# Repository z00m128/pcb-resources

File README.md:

# My PCB library 
Here is the set of printed circuit boards created by me over a time. I used mostly KiCad (PCBs created from scratch) or Sprint-Layout 6.0 (PCBs recreated from scans or photos).

## [ZX Spectrum 128k replica](https://github.com/z00m128/pcb-resources/tree/main/Toastrack)
Recreated PCB of ZX Spectrum 128k. I felt sorry for the Toastrack owner who contacted me with a repair request and who fell victim to eBay fraud, so I decided to make a replica.

## [ZX Cherry Keyboard](https://github.com/z00m128/pcb-resources/blob/main/ZX-Cherry-KB/)
Another iteration of a mechanical keyboard for the ZX Spectrum. This time my own, designed for one of my projects, but it is compatible with +2/+3 case.

## [Didaktik M'92](https://github.com/z00m128/pcb-resources/tree/main/Didaktik-M-92)
A clone of the ZX Spectrum computer manufactured by the Slovak company Didaktik v.d. in the early 1990s. The recreated PCB has been verified and is functional.

## [Didaktik Kompakt, revision 2.3](https://github.com/z00m128/pcb-resources/tree/main/Didaktik-Kompakt-ver23)
A clone of the ZX Spectrum computer manufactured by the Slovak company Didaktik v.d. in the early 1990s. This clone is actually a Didaktik M with a built-in D80 disk system running the MDOS operating system. The recreated PCB has been verified and is functional.

## Melodik 2, revisions [1.0](https://github.com/z00m128/pcb-resources/tree/main/Melodik2/v1.0), [1.1](https://github.com/z00m128/pcb-resources/tree/main/Melodik2/v1.1) and [2.0](https://github.com/z00m128/pcb-resources/tree/main/Melodik2/v2.0)
Melodik was an audio interface for the ZX Spectrum and compatibles, manufactured by Didaktik v.d. during the 1990s. It was of poor quality, suffered from several ailments and broke down. These were my 3 attempts to recreate it so that the result fit into the original box. The revisions differ only minimally and are a consequence of KiCad not being able to properly open projects created in its older versions. All have a fixed oscillator error, removed collision with D40 / D80 / Kompakt floppy controllers. The latest revision 2.0 is not tested but should be functional. It has an added filter in the LM386 power supply.

## KeyFace
A PS/2 keyboard interface for ZX Spectrum, [internal](https://github.com/z00m128/pcb-resources/tree/main/KeyFace) and [external](https://github.com/z00m128/pcb-resources/tree/main/KeyFace-external) versions. Both were developed by MDV in late 90's for Kompakt Servis company. Both PCBs are verified and working.

## [Lamac CPM](https://github.com/z00m128/pcb-resources/tree/main/Lamac-CPM)
A board used to modify a ZX Spectrum computer to expand memory (80k-256k) for use with CP/M. It was common modification in former Czechoslovakia, well documented in local electronics magazine. This PCB was not vertified yet.

## [PMD ColorAce](https://github.com/z00m128/pcb-resources/tree/main/PMD-ColorAce)
Hardware modification for PMD85 computer. It extends its capabilities and allows to display 7 different colors on the black background. This is my own iteration of PCB. It was not verified yet.

## [PMD KeyFace](https://github.com/z00m128/pcb-resources/tree/main/PMD-KeyFace)
PS/2 keyboard interface for PMD85 computer. This is my own iteration of PCB. It was not verified yet.

## [Kicad libraries](https://github.com/z00m128/pcb-resources/tree/main/KiCad-libs)
Set of libraries for KiCad 6.0 and newer that you may need if you want to edit some of my projects.

_GAL20V8, GAL22V10, AY-3-8912, AY-3-8910, ZX Spectrum expansion connector._

---

## NOTICE
The production of these printed circuit boards for profit is strictly prohibited. See [license](LICENSE.md).

## Disclaimer
_All PCBs posted here are just my hobby projects and not professional designs. They may contain errors, glitches, or other unforeseen problems. Some of them have been tested quite extensively, but I make no warranties as to functionality or fitness for a particular purpose. If you connect any of these products to any of your equipment, you do so entirely at your own risk and I am not responsible for any damages._

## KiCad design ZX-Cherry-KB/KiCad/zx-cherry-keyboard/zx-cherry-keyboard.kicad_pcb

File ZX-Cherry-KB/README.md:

# ZX Cherry Keyboard

I needed a proper mechanical keyboard for one of my projects and none of the freely available solutions suited me. So I decided to design my own keyboard, but in a way that it would be usable elsewhere, not just in my project. This keyboard is compatible with the ZX Spectrum +2 (gray) and should work also with other ZX Spectrums and clones. With ZX Spectrum +2A/+3 it is not tested, but the base matrix is connected identical to other Spectrums, so it should work too.

Due to the hard-to-find 4.5u spacebar, the key layout has been changed to the easier-to-find 6.25u spacebar. I also swapped the BREAK and DELETE keys and moved EDIT and other keys to make it more comfortable for me.

With [these](https://www.thingiverse.com/thing:4978541) keycaps it fits nicely to +2 case, see the prototype photos below.

## Top Layer

## Bottom Layer

## Custom Layout

## Prototype pictures

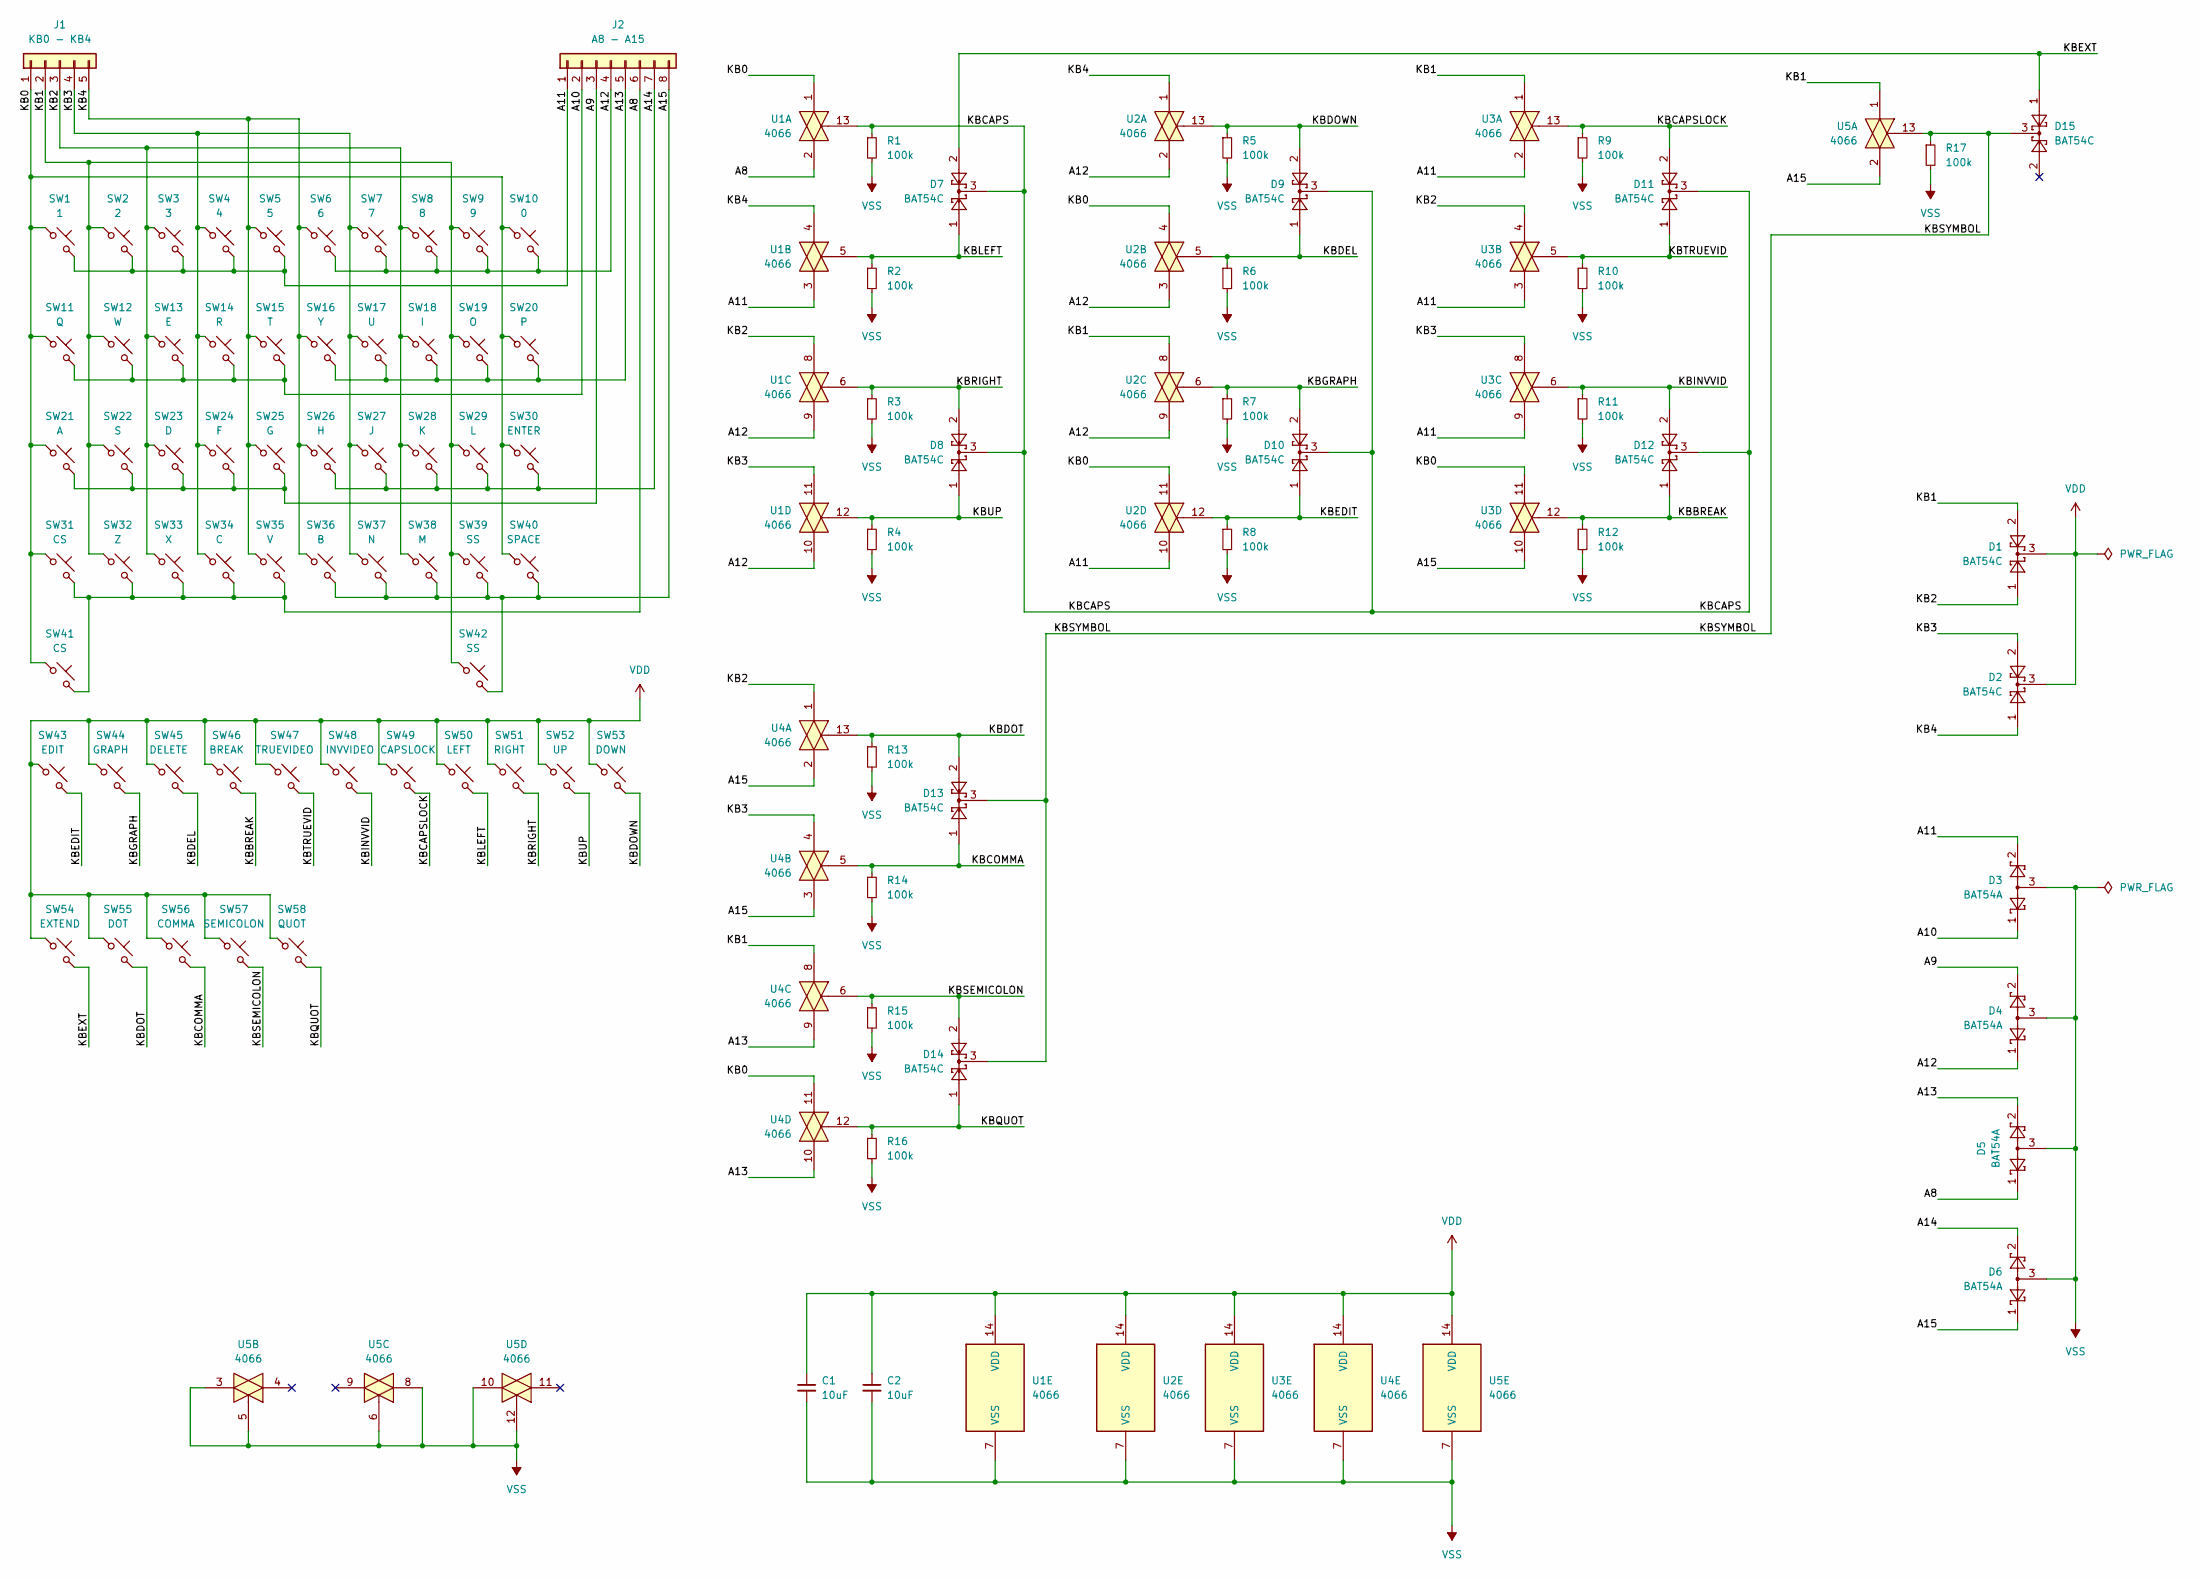
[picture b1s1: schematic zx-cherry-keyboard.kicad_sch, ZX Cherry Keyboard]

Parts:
C1, C2: 10uF; C_1210_3225Metric_Pad1.33x2.70mm_HandSolder
D1, D2, D7, D8, D9, D10, D11, D12, D13, D14, D15: BAT54C; SOT-23
D3, D4, D5, D6: BAT54A; SOT-23
J1: KB0 - KB4; PinHeader_1x05_P2.54mm_Horizontal
J2: A8 - A15; PinHeader_1x08_P2.54mm_Horizontal
R1, R2, R3, R4, R5, R6, R7, R8, R9, R10, R11, R12, R13, R14, R15, R16, R17: 100k; R_1206_3216Metric_Pad1.30x1.75mm_HandSolder
SW1: 1; SW_Cherry_MX_1.00u_PCB
SW2: 2; SW_Cherry_MX_1.00u_PCB
SW3: 3; SW_Cherry_MX_1.00u_PCB
SW4: 4; SW_Cherry_MX_1.00u_PCB
SW5: 5; SW_Cherry_MX_1.00u_PCB
SW6: 6; SW_Cherry_MX_1.00u_PCB
SW7: 7; SW_Cherry_MX_1.00u_PCB
SW8: 8; SW_Cherry_MX_1.00u_PCB
SW9: 9; SW_Cherry_MX_1.00u_PCB
SW10: 0; SW_Cherry_MX_1.00u_PCB
SW11: Q; SW_Cherry_MX_1.00u_PCB
SW12: W; SW_Cherry_MX_1.00u_PCB
SW13: E; SW_Cherry_MX_1.00u_PCB
SW14: R; SW_Cherry_MX_1.00u_PCB
SW15: T; SW_Cherry_MX_1.00u_PCB
SW16: Y; SW_Cherry_MX_1.00u_PCB
SW17: U; SW_Cherry_MX_1.00u_PCB
SW18: I; SW_Cherry_MX_1.00u_PCB
SW19: O; SW_Cherry_MX_1.00u_PCB
SW20: P; SW_Cherry_MX_1.00u_PCB
SW21: A; SW_Cherry_MX_1.00u_PCB
SW22: S; SW_Cherry_MX_1.00u_PCB
SW23: D; SW_Cherry_MX_1.00u_PCB
SW24: F; SW_Cherry_MX_1.00u_PCB
SW25: G; SW_Cherry_MX_1.00u_PCB
SW26: H; SW_Cherry_MX_1.00u_PCB
SW27: J; SW_Cherry_MX_1.00u_PCB
SW28: K; SW_Cherry_MX_1.00u_PCB
SW29: L; SW_Cherry_MX_1.00u_PCB
SW30: ENTER; SW_Cherry_MX_1.75u_PCB
SW31: CS; SW_Cherry_MX_1.75u_PCB
SW32: Z; SW_Cherry_MX_1.00u_PCB
SW33: X; SW_Cherry_MX_1.00u_PCB
SW34: C; SW_Cherry_MX_1.00u_PCB
SW35: V; SW_Cherry_MX_1.00u_PCB
SW36: B; SW_Cherry_MX_1.00u_PCB
SW37: N; SW_Cherry_MX_1.00u_PCB
SW38: M; SW_Cherry_MX_1.00u_PCB
SW39, SW42: SS; SW_Cherry_MX_1.00u_PCB
SW40: SPACE; SW_Cherry_MX_6.25u_PCB
SW41: CS; SW_Cherry_MX_1.50u_PCB
SW43: EDIT; SW_Cherry_MX_1.00u_PCB
SW44: GRAPH; SW_Cherry_MX_1.00u_PCB
SW45: DELETE; SW_Cherry_MX_1.25u_PCB
SW46: BREAK; SW_Cherry_MX_1.25u_PCB
SW47: TRUEVIDEO; SW_Cherry_MX_1.00u_PCB
SW48: INVVIDEO; SW_Cherry_MX_1.00u_PCB
SW49: CAPSLOCK; SW_Cherry_MX_1.00u_PCB
SW50: LEFT; SW_Cherry_MX_1.00u_PCB
SW51: RIGHT; SW_Cherry_MX_1.00u_PCB
SW52: UP; SW_Cherry_MX_1.00u_PCB
SW53: DOWN; SW_Cherry_MX_1.00u_PCB
SW54: EXTEND; SW_Cherry_MX_1.50u_PCB
SW55: DOT; SW_Cherry_MX_1.00u_PCB
SW56: COMMA; SW_Cherry_MX_1.00u_PCB
SW57: SEMICOLON; SW_Cherry_MX_1.00u_PCB
SW58: QUOT; SW_Cherry_MX_1.00u_PCB
U1, U2, U3, U4, U5: 4066; SO-14_5.3x10.2mm_P1.27mm

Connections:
/A8: D5.1, J2.6, SW31.2, SW32.2, SW33.2, SW34.2, SW35.2, SW41.2, U1.2
/A9: D4.2, J2.3, SW21.2, SW22.2, SW23.2, SW24.2, SW25.2
/A10: D3.1, J2.2, SW11.2, SW12.2, SW13.2, SW14.2, SW15.2
/A11: D3.2, J2.1, SW1.2, SW2.2, SW3.2, SW4.2, SW5.2, U1.3, U2.10, U3.2, U3.3, U3.9
/A12: D4.1, J2.4, SW6.2, SW7.2, SW8.2, SW9.2, SW10.2, U1.9, U1.10, U2.2, U2.3, U2.9
/A13: D5.2, J2.5, SW16.2, SW17.2, SW18.2, SW19.2, SW20.2, U4.9, U4.10
/A14: D6.2, J2.7, SW26.2, SW27.2, SW28.2, SW29.2, SW30.2
/A15: D6.1, J2.8, SW36.2, SW37.2, SW38.2, SW39.2, SW40.2, SW42.2, U3.10, U4.2, U4.3, U5.2
/KB0: J1.1, SW1.1, SW10.1, SW11.1, SW20.1, SW21.1, SW30.1, SW31.1, SW40.1, SW41.1, U1.1, U2.4, U2.11, U3.11, U4.11
/KB1: D1.2, J1.2, SW2.1, SW9.1, SW12.1, SW19.1, SW22.1, SW29.1, SW32.1, SW39.1, SW42.1, U2.8, U3.1, U4.8, U5.1
/KB2: D1.1, J1.3, SW3.1, SW8.1, SW13.1, SW18.1, SW23.1, SW28.1, SW33.1, SW38.1, U1.8, U3.4, U4.1
/KB3: D2.2, J1.4, SW4.1, SW7.1, SW14.1, SW17.1, SW24.1, SW27.1, SW34.1, SW37.1, U1.11, U3.8, U4.4
/KB4: D2.1, J1.5, SW5.1, SW6.1, SW15.1, SW16.1, SW25.1, SW26.1, SW35.1, SW36.1, U1.4, U2.1
/KBBREAK: D12.1, R12.1, SW46.2, U3.12
/KBCAPS: D7.3, D8.3, D9.3, D10.3, D11.3, D12.3, R1.1, U1.13
/KBCAPSLOCK: D11.2, R9.1, SW49.2, U3.13
/KBCOMMA: D13.1, R14.1, SW56.2, U4.5
/KBDEL: D9.1, R6.1, SW45.2, U2.5
/KBDOT: D13.2, R13.1, SW55.2, U4.13
/KBDOWN: D9.2, R5.1, SW53.2, U2.13
/KBEDIT: D10.1, R8.1, SW43.2, U2.12
/KBEXT: D7.2, D15.1, SW54.2
/KBGRAPH: D10.2, R7.1, SW44.2, U2.6
/KBINVVID: D12.2, R11.1, SW48.2, U3.6
/KBLEFT: D7.1, R2.1, SW50.2, U1.5
/KBQUOT: D14.1, R16.1, SW58.2, U4.12
/KBRIGHT: D8.2, R3.1, SW51.2, U1.6
/KBSEMICOLON: D14.2, R15.1, SW57.2, U4.6
/KBSYMBOL: D13.3, D14.3, D15.3, R17.1, U5.13
/KBTRUEVID: D11.1, R10.1, SW47.2, U3.5
/KBUP: D8.1, R4.1, SW52.2, U1.12
VDD: C1.1, C2.1, D1.3, D2.3, SW43.1, SW44.1, SW45.1, SW46.1, SW47.1, SW48.1, SW49.1, SW50.1, SW51.1, SW52.1, SW53.1, SW54.1, SW55.1, SW56.1, SW57.1, SW58.1, U1.14 (VDD), U2.14 (VDD), U3.14 (VDD), U4.14 (VDD), U5.14 (VDD)
VSS: C1.2, C2.2, D3.3, D4.3, D5.3, D6.3, R1.2, R2.2, R3.2, R4.2, R5.2, R6.2, R7.2, R8.2, R9.2, R10.2, R11.2, R12.2, R13.2, R14.2, R15.2, R16.2, R17.2, U1.7 (VSS), U2.7 (VSS), U3.7 (VSS), U4.7 (VSS), U5.3, U5.5, U5.6, U5.7 (VSS), U5.8, U5.10, U5.12

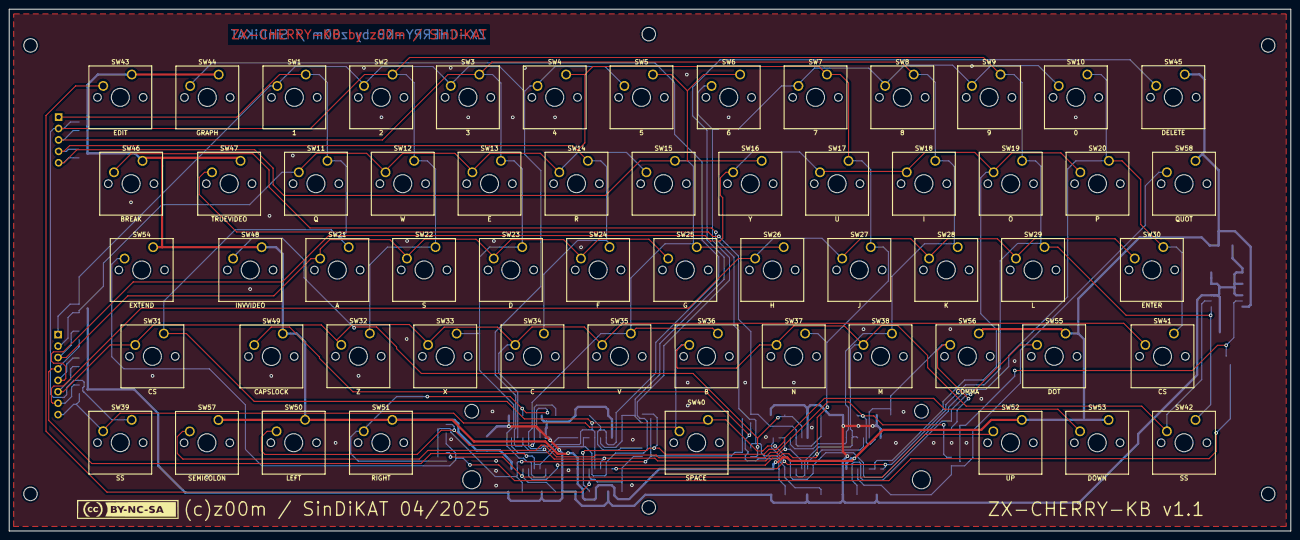
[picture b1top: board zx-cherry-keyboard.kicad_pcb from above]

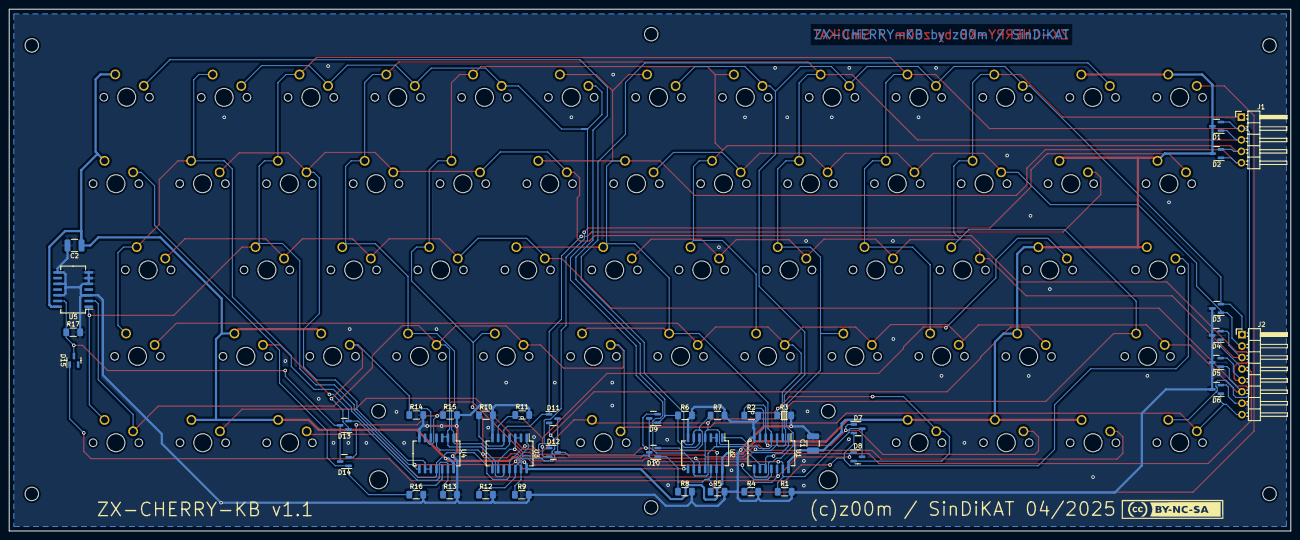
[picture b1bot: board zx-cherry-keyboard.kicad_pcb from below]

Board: 2 copper layers, 285.0 x 116.0 mm, 101 parts (42 on the bottom side), 33 nets.

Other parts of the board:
G01, G02: LOGO; cc-by-nc-sa

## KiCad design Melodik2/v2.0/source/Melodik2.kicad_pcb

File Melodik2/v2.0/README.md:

# Melodik2 rev 2.0

Melodik was AY interface for ZX Spectrum and compatibles, produced by Didaktik v.d. in 90's. This is my third attempt at making a replacement, as the original PCB was of terrible quality, was breaking down, and the main oscillator tended to start at all sorts of frequencies, just not the right one. The PCB is not verified yet, but it should work.

# Schematic diagram

## 3D rendering

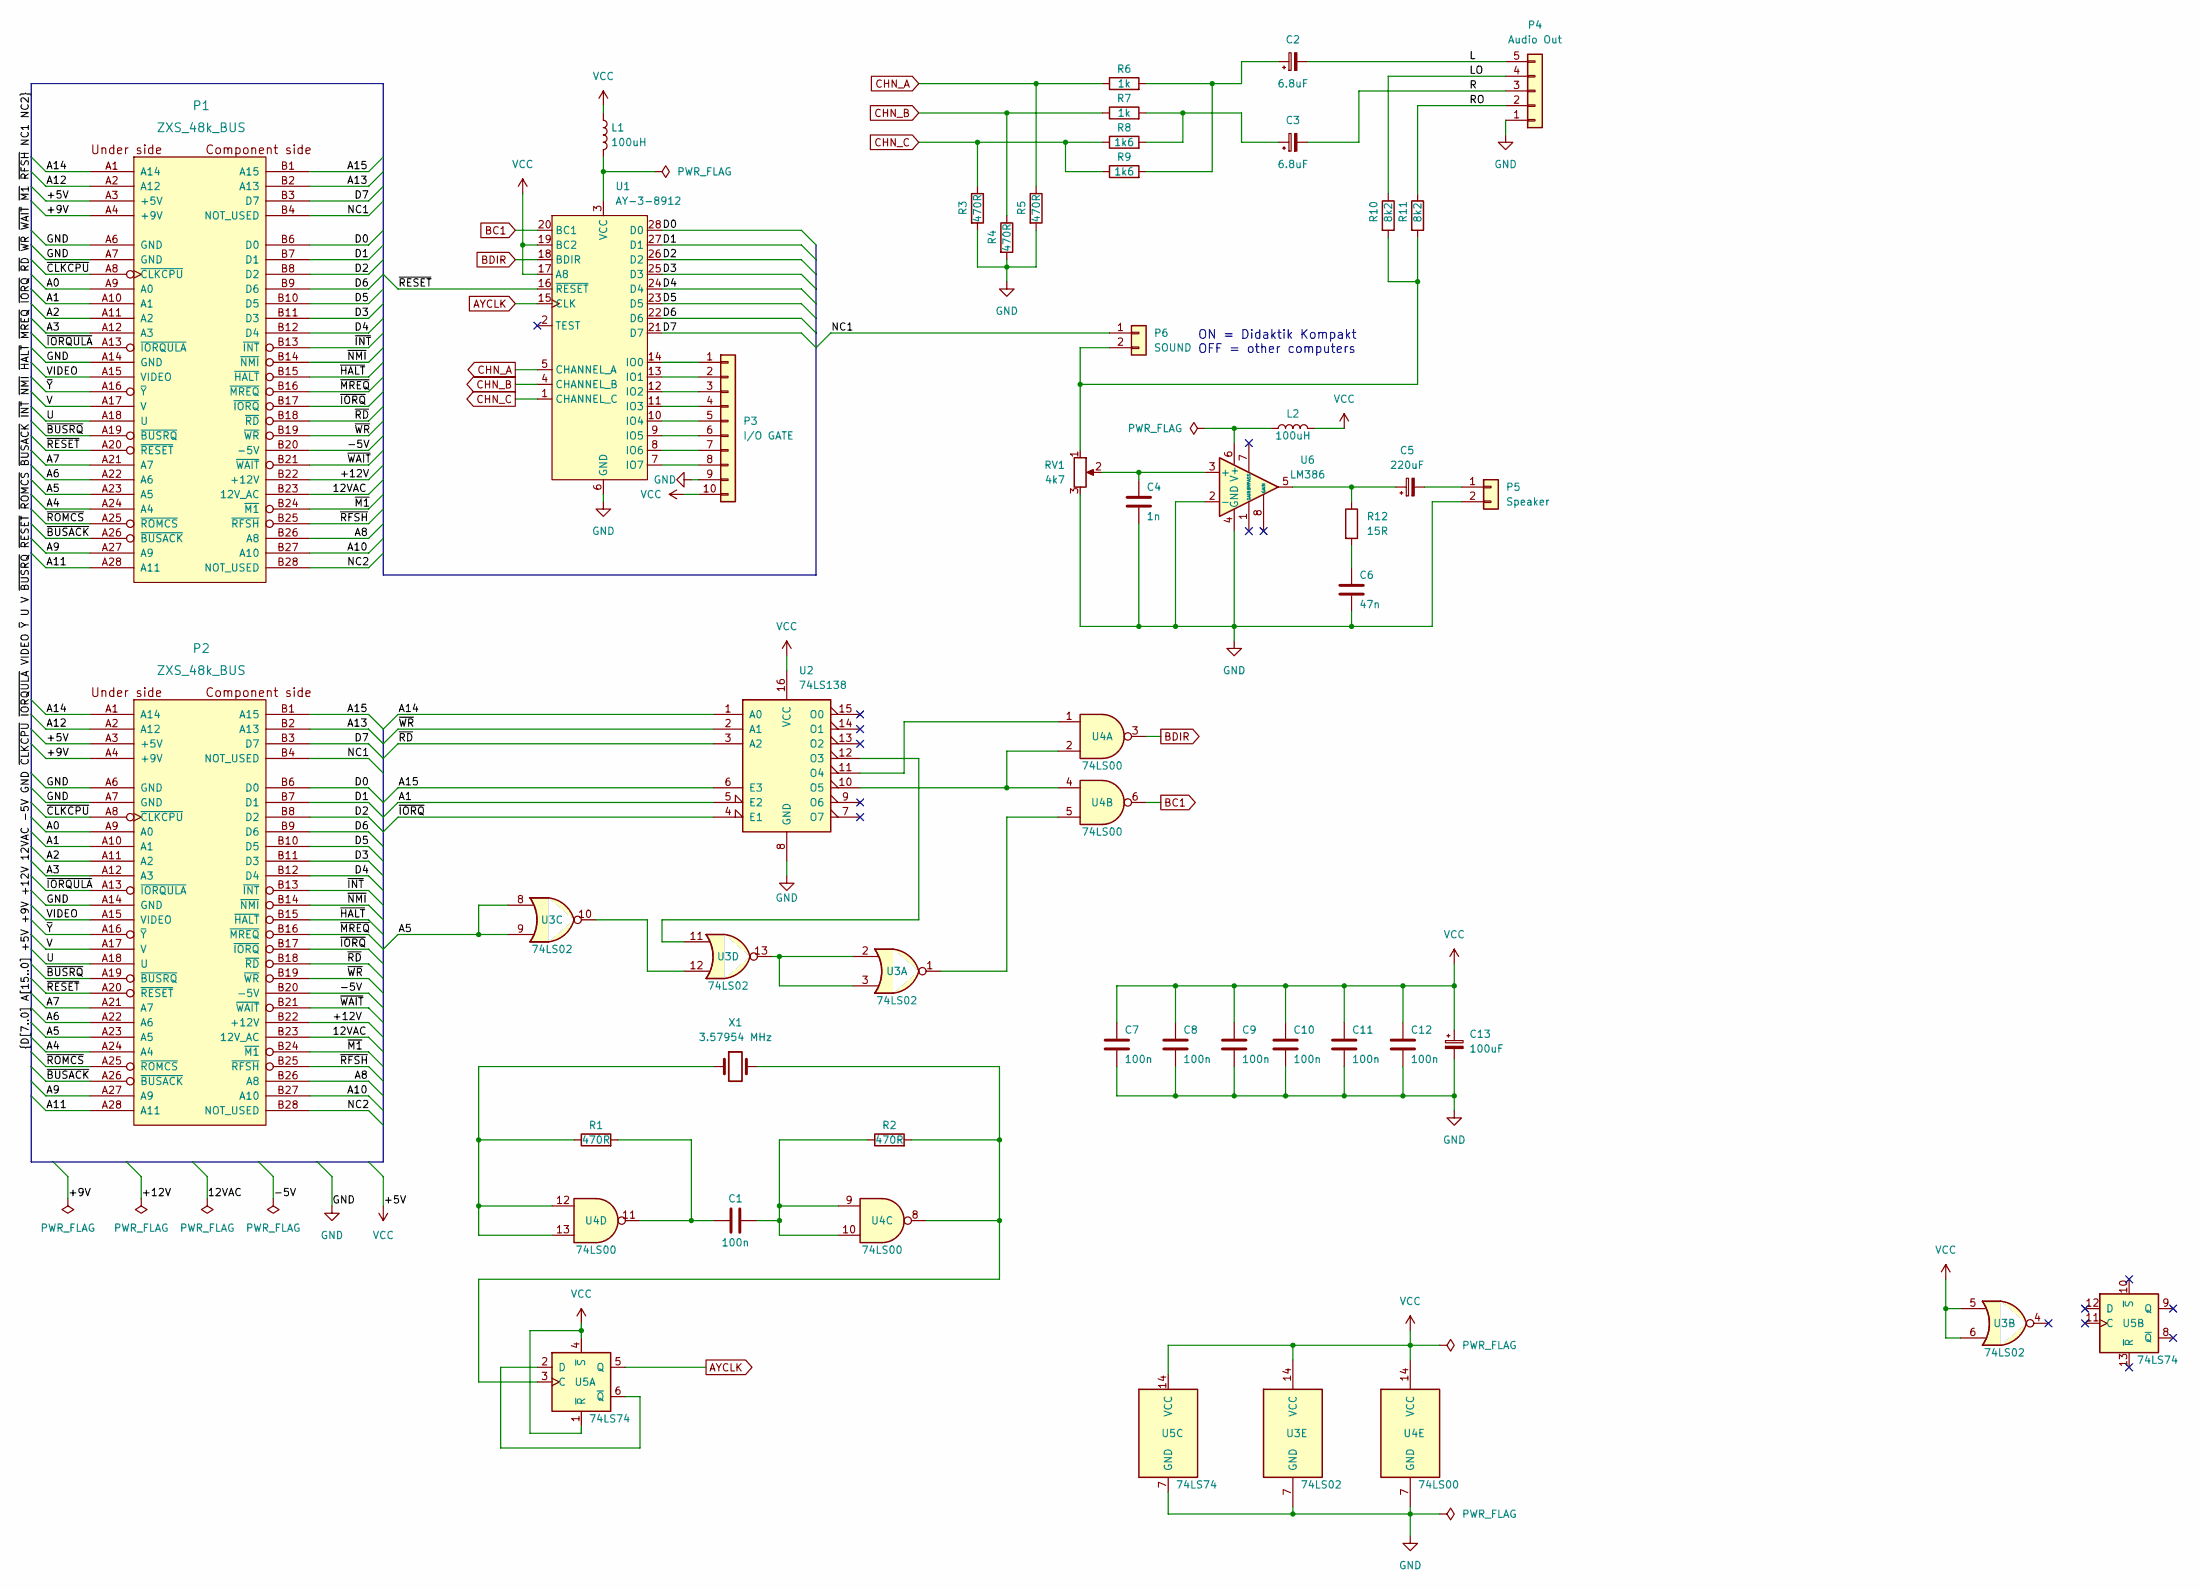
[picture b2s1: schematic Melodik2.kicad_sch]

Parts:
C1, C7, C8, C9, C10, C11, C12: 100n; C_Disc_D5.0mm_W2.5mm_P5.00mm
C2, C3: 6.8uF; CP_Radial_D5.0mm_P2.50mm
C4: 1n; C_Disc_D5.0mm_W2.5mm_P5.00mm
C5: 220uF; CP_Radial_D8.0mm_P3.80mm
C6: 47n; C_Disc_D5.0mm_W2.5mm_P5.00mm
C13: 100uF; CP_Radial_D8.0mm_P3.50mm
L1, L2: 100uH; R_Axial_DIN0207_L6.3mm_D2.5mm_P10.16mm_Horizontal
P1, P2: ZXS_48k_BUS; zxs48kbus
P3: I/O GATE; PinHeader_1x10_P2.54mm_Vertical
P4: Audio Out; PinHeader_1x05_P2.54mm_Vertical
P5: Speaker; PinHeader_1x02_P2.54mm_Vertical
P6: SOUND; PinHeader_1x02_P2.54mm_Vertical
R1, R2, R3, R4, R5: 470R; R_Axial_DIN0207_L6.3mm_D2.5mm_P7.62mm_Horizontal
R6, R7: 1k; R_Axial_DIN0207_L6.3mm_D2.5mm_P7.62mm_Horizontal
R8, R9: 1k6; R_Axial_DIN0207_L6.3mm_D2.5mm_P7.62mm_Horizontal
R10, R11: 8k2; R_Axial_DIN0207_L6.3mm_D2.5mm_P7.62mm_Horizontal
R12: 15R; R_Axial_DIN0207_L6.3mm_D2.5mm_P7.62mm_Horizontal
RV1: 4k7; PinHeader_1x03_P2.54mm_Vertical
U1: AY-3-8912; DIP-28_W15.24mm
U2: 74LS138; DIP-16_W7.62mm
U3: 74LS02; DIP-14_W7.62mm
U4: 74LS00; DIP-14_W7.62mm
U5: 74LS74; DIP-14_W7.62mm
U6: LM386; DIP-8_W7.62mm
X1: 3.57954 MHz; Crystal_HC49-U_Vertical

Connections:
/12VAC: P1.B23 (12V_AC), P2.B23 (12V_AC)
/+9V: P1.A4 (+9V), P2.A4 (+9V)
/+12V: P1.B22 (+12V), P2.B22 (+12V)
/-5V: P1.B20 (-5V), P2.B20 (-5V)
/A0: P1.A9 (A0), P2.A9 (A0)
/A1: P1.A10 (A1), P2.A10 (A1), U2.5 (E2)
/A2: P1.A11 (A2), P2.A11 (A2)
/A3: P1.A12 (A3), P2.A12 (A3)
/A4: P1.A24 (A4), P2.A24 (A4)
/A5: P1.A23 (A5), P2.A23 (A5), U3.8, U3.9
/A6: P1.A22 (A6), P2.A22 (A6)
/A7: P1.A21 (A7), P2.A21 (A7)
/A8: P1.B26 (A8), P2.B26 (A8)
/A9: P1.A27 (A9), P2.A27 (A9)
/A10: P1.B27 (A10), P2.B27 (A10)
/A11: P1.A28 (A11), P2.A28 (A11)
/A12: P1.A2 (A12), P2.A2 (A12)
/A13: P1.B2 (A13), P2.B2 (A13)
/A14: P1.A1 (A14), P2.A1 (A14), U2.1 (A0)
/A15: P1.B1 (A15), P2.B1 (A15), U2.6 (E3)
/D0: P1.B6 (D0), P2.B6 (D0), U1.28 (D0)
/D1: P1.B7 (D1), P2.B7 (D1), U1.27 (D1)
/D2: P1.B8 (D2), P2.B8 (D2), U1.26 (D2)
/D3: P1.B11 (D3), P2.B11 (D3), U1.25 (D3)
/D4: P1.B12 (D4), P2.B12 (D4), U1.24 (D4)
/D5: P1.B10 (D5), P2.B10 (D5), U1.23 (D5)
/D6: P1.B9 (D6), P2.B9 (D6), U1.22 (D6)
/D7: P1.B3 (D7), P2.B3 (D7), U1.21 (D7)
/L: C2.2, P4.5
/LO: P4.4, R10.1
/NC1: P1.B4 (NOT_USED), P2.B4 (NOT_USED), P6.1
/NC2: P1.B28 (NOT_USED), P2.B28 (NOT_USED)
/R: C3.2, P4.3
/RO: P4.2, R11.1
/U: P1.A18 (U), P2.A18 (U)
/V: P1.A17 (V), P2.A17 (V)
/VIDEO: P1.A15 (VIDEO), P2.A15 (VIDEO)
/~BUSACK: P1.A26 (~BUSACK), P2.A26 (~BUSACK)
/~BUSRQ: P1.A19 (~BUSRQ), P2.A19 (~BUSRQ)
/~CLKCPU: P1.A8 (~CLKCPU), P2.A8 (~CLKCPU)
/~HALT: P1.B15 (~HALT), P2.B15 (~HALT)
/~INT: P1.B13 (~INT), P2.B13 (~INT)
/~IORQULA: P1.A13 (~IORQULA), P2.A13 (~IORQULA)
/~IORQ: P1.B17 (~IORQ), P2.B17 (~IORQ), U2.4 (E1)
/~M1: P1.B24 (~M1), P2.B24 (~M1)
/~MREQ: P1.B16 (~MREQ), P2.B16 (~MREQ)
/~NMI: P1.B14 (~NMI), P2.B14 (~NMI)
/~RD: P1.B18 (~RD), P2.B18 (~RD), U2.3 (A2)
/~RESET: P1.A20 (~RESET), P2.A20 (~RESET), U1.16 (~RESET)
/~RFSH: P1.B25 (~RFSH), P2.B25 (~RFSH)
/~ROMCS: P1.A25 (~ROMCS), P2.A25 (~ROMCS)
/~WAIT: P1.B21 (~WAIT), P2.B21 (~WAIT)
/~WR: P1.B19 (~WR), P2.B19 (~WR), U2.2 (A1)
/~Y: P1.A16 (~Y), P2.A16 (~Y)
AYCLK: U1.15 (CLK), U5.5 (Q)
BC1: U1.20 (BC1), U4.6
BDIR: U1.18 (BDIR), U4.3
CHN_A: R5.1, R6.1, U1.5 (CHANNEL_A)
CHN_B: R4.1, R7.1, U1.4 (CHANNEL_B)
CHN_C: R3.1, R8.1, R9.1, U1.1 (CHANNEL_C)
GND: C4.2, C6.2, C7.2, C8.2, C9.2, C10.2, C11.2, C12.2, C13.2, P1.A6 (GND), P1.A7 (GND), P1.A14 (GND), P2.A6 (GND), P2.A7 (GND), P2.A14 (GND), P3.9, P4.1, P5.2, R3.2, R4.2, R5.2, RV1.3, U1.6 (GND), U2.8 (GND), U3.7 (GND), U4.7 (GND), U5.7 (GND), U6.2 (-), U6.4 (GND)
unnamed: C1.1, R1.2, U4.11
unnamed: C1.2, R2.1, U4.9, U4.10
unnamed: C2.1, R6.2, R9.2
unnamed: C3.1, R7.2, R8.2
unnamed: C4.1, RV1.2, U6.3 (+)
unnamed: C5.1, R12.1, U6.5
unnamed: C5.2, P5.1
unnamed: C6.1, R12.2
unnamed: L1.2, U1.3 (VCC)
unnamed: L2.1, U6.6 (V+)
unnamed: P3.1, U1.14 (IO0)
unnamed: P3.2, U1.13 (IO1)
unnamed: P3.3, U1.12 (IO2)
unnamed: P3.4, U1.11 (IO3)
unnamed: P3.5, U1.10 (IO4)
unnamed: P3.6, U1.9 (IO5)
unnamed: P3.7, U1.8 (IO6)
unnamed: P3.8, U1.7 (IO7)
unnamed: P6.2, R10.2, R11.2, RV1.1
unnamed: R1.1, U4.12, U4.13, X1.1
unnamed: R2.2, U4.8, U5.3 (C), X1.2
unnamed: U2.10 (O5), U4.2, U4.4
unnamed: U2.11 (O4), U4.1
unnamed: U2.12 (O3), U3.11
unnamed: U3.1, U4.5
unnamed: U3.10, U3.12
unnamed: U3.2, U3.3, U3.13
unnamed: U5.2 (D), U5.6 (~Q)
VCC: C7.1, C8.1, C9.1, C10.1, C11.1, C12.1, C13.1, L1.1, L2.2, P1.A3 (+5V), P2.A3 (+5V), P3.10, U1.17 (A8), U1.19 (BC2), U2.16 (VCC), U3.5, U3.6, U3.14 (VCC), U4.14 (VCC), U5.1 (~R), U5.4 (~S), U5.14 (VCC)

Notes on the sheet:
ON = Didaktik Kompakt OFF = other computers

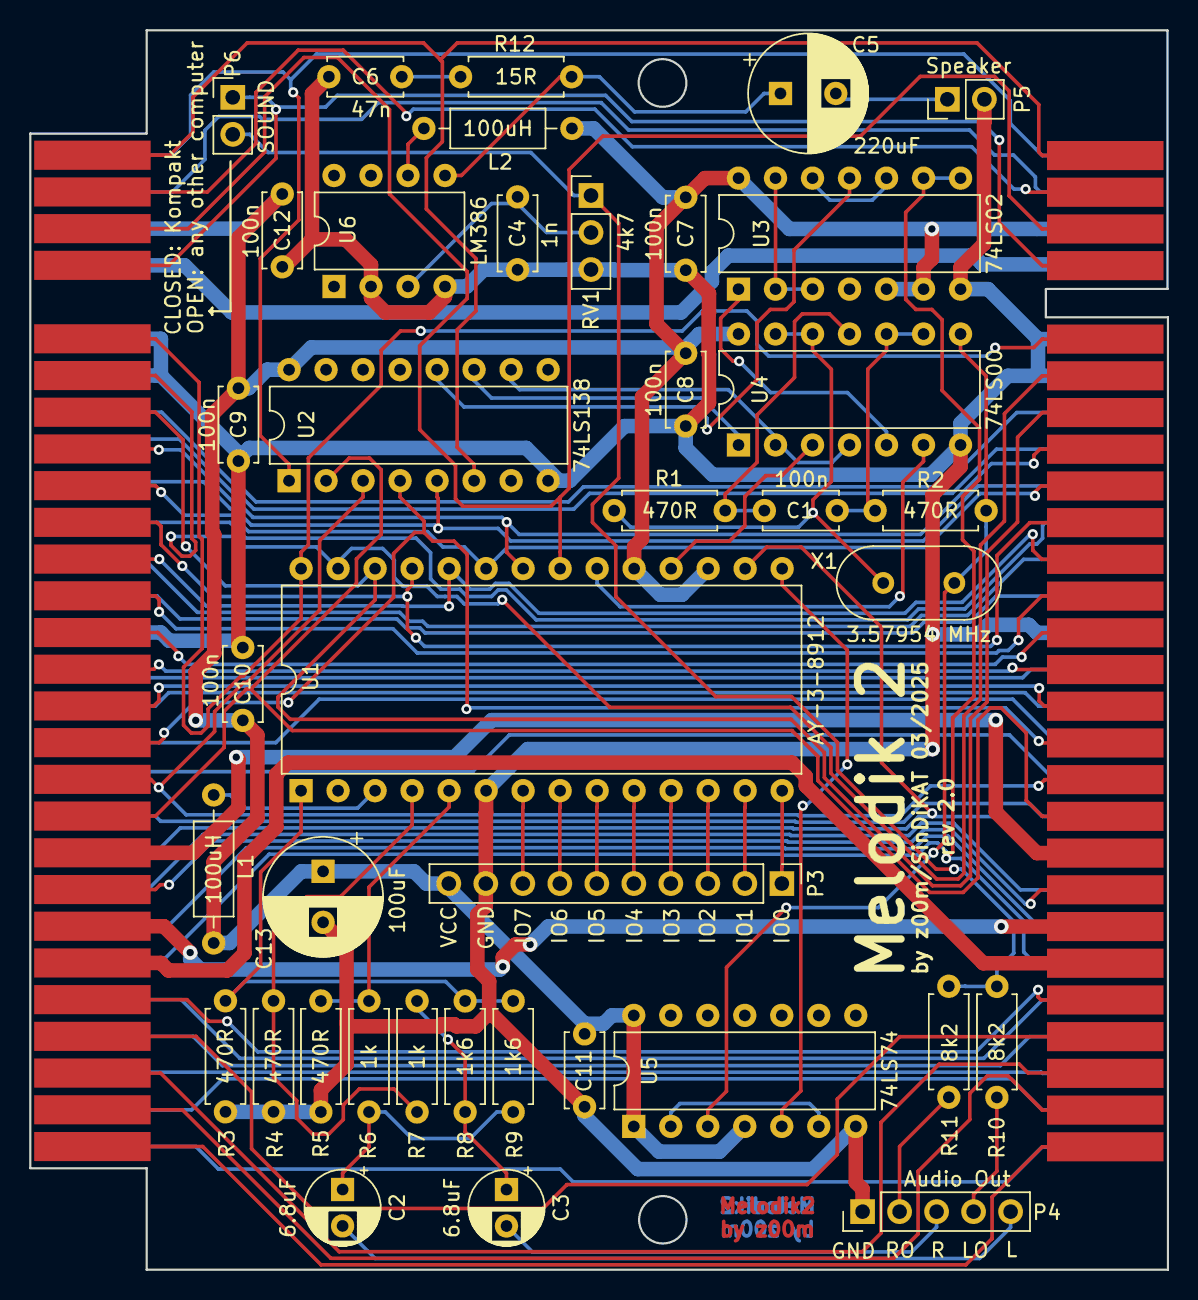
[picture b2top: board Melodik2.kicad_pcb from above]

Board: 2 copper layers, 78.1 x 85.1 mm, 41 parts (0 on the bottom side), 90 nets.

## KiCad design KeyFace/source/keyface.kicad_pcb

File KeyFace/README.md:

# KeyFace for ZX Spectrum
A PS/2 keyboard interface for ZX Spectrum, riginally made by MDV for Kompakt Servis company. This PCB was recreated using original PCB from Kompakt Servis. It is verified and known as working.

## Schematic Diagram

## Populated PCB

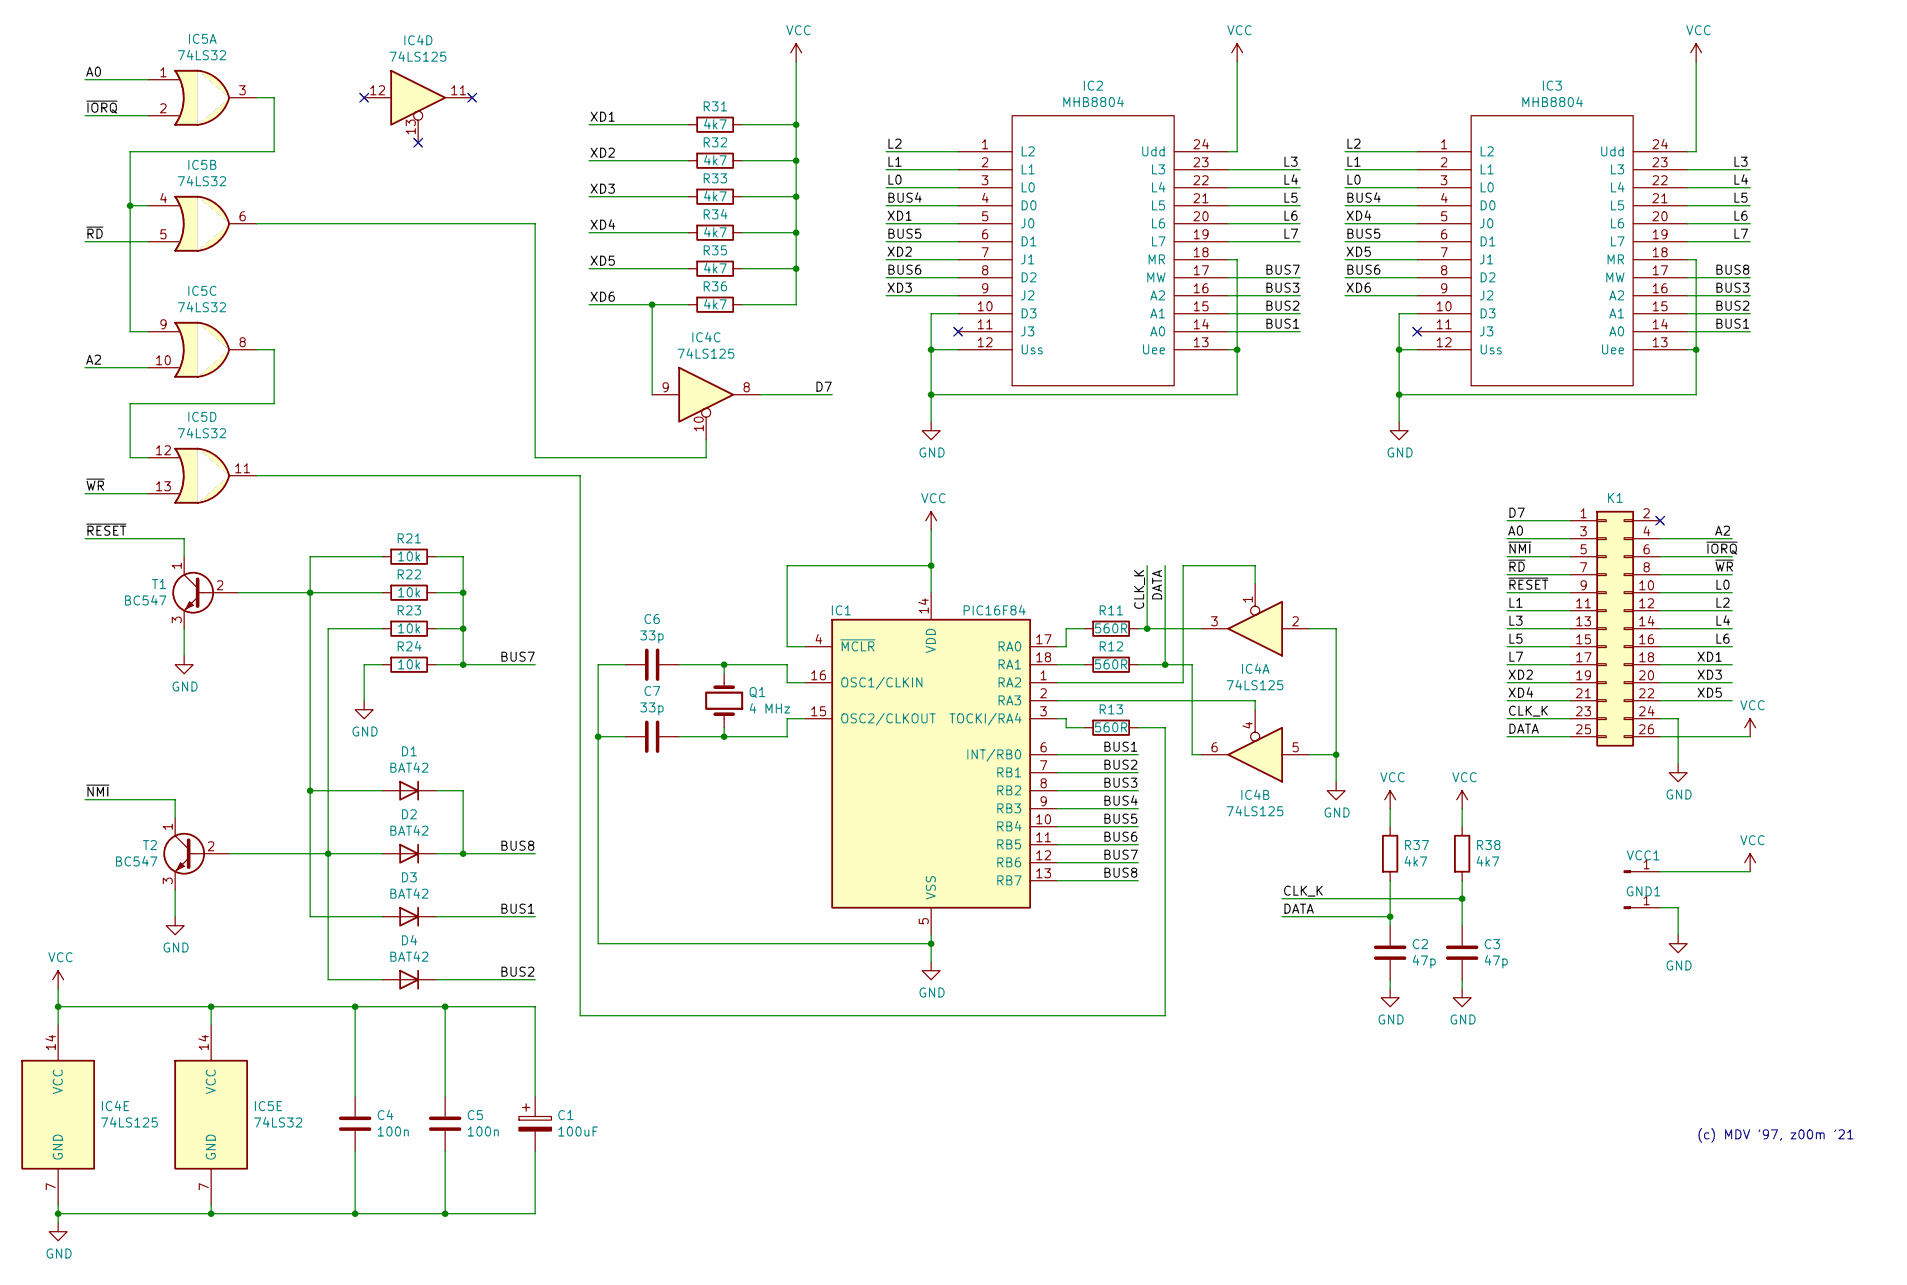
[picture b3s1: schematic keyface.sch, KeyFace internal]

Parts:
C1: 100uF; CP_Radial_D6.3mm_P2.50mm
C2, C3: 47p; C_Disc_D3.0mm_W2.0mm_P2.50mm
C4, C5: 100n; C_Disc_D4.3mm_W1.9mm_P5.00mm
C6, C7: 33p; C_Disc_D3.0mm_W2.0mm_P2.50mm
D1, D2, D3, D4: BAT42; D_DO-34_SOD68_P10.16mm_Horizontal
GND1: Conn_01x01_Male; Pin_D1.0mm_L10.0mm
IC1: PIC16F84; DIP-18_W7.62mm
IC2, IC3: MHB8804; DIP-24_W15.24mm
IC4: 74LS125; DIP-14_W7.62mm
IC5: 74LS32; DIP-14_W7.62mm
K1: Conn_02x13_Odd_Even; PinHeader_2x13_P2.54mm_Vertical
Q1: 4 MHz; Crystal_HC49-U_Vertical
R11, R12, R13: 560R; R_Axial_DIN0204_L3.6mm_D1.6mm_P2.54mm_Vertical
R21, R22, R23, R24: 10k; R_Axial_DIN0204_L3.6mm_D1.6mm_P2.54mm_Vertical
R31, R32, R33, R34, R35, R36, R37, R38: 4k7; R_Axial_DIN0204_L3.6mm_D1.6mm_P2.54mm_Vertical
T1, T2: BC547; TO-92
VCC1: Conn_01x01_Male; Pin_D1.0mm_L10.0mm

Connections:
/A0: IC5.1, K1.3
/A2: IC5.10, K1.4
/BUS1: D3.1 (K), IC1.6 (INT/RB0), IC2.14 (A0), IC3.14 (A0)
/BUS2: D4.1 (K), IC1.7 (RB1), IC2.15 (A1), IC3.15 (A1)
/BUS3: IC1.8 (RB2), IC2.16 (A2), IC3.16 (A2)
/BUS4: IC1.9 (RB3), IC2.4 (D0), IC3.4 (D0)
/BUS5: IC1.10 (RB4), IC2.6 (D1), IC3.6 (D1)
/BUS6: IC1.11 (RB5), IC2.8 (D2), IC3.8 (D2)
/BUS7: IC1.12 (RB6), IC2.17 (MW), R21.1, R22.1, R23.1, R24.1
/BUS8: D1.1 (K), D2.1 (K), IC1.13 (RB7), IC3.17 (MW)
/CLK_K: C3.1, IC4.3, K1.23, R11.1, R38.2
/D7: IC4.8, K1.1
/DATA: C2.1, IC4.6, K1.25, R12.1, R37.2
/L0: IC2.3 (L0), IC3.3 (L0), K1.10
/L1: IC2.2 (L1), IC3.2 (L1), K1.11
/L2: IC2.1 (L2), IC3.1 (L2), K1.12
/L3: IC2.23 (L3), IC3.23 (L3), K1.13
/L4: IC2.22 (L4), IC3.22 (L4), K1.14
/L5: IC2.21 (L5), IC3.21 (L5), K1.15
/L6: IC2.20 (L6), IC3.20 (L6), K1.16
/L7: IC2.19 (L7), IC3.19 (L7), K1.17
/XD1: IC2.5 (J0), K1.18, R31.2
/XD2: IC2.7 (J1), K1.19, R32.2
/XD3: IC2.9 (J2), K1.20, R33.2
/XD4: IC3.5 (J0), K1.21, R34.2
/XD5: IC3.7 (J1), K1.22, R35.2
/XD6: IC3.9 (J2), IC4.9, R36.2
/~IORQ: IC5.2, K1.6
/~NMI: K1.5, T2.1 (C)
/~RD: IC5.5, K1.7
/~RESET: K1.9, T1.1 (C)
/~WR: IC5.13, K1.8
GND: C1.2, C2.2, C3.2, C4.2, C5.2, C6.2, C7.2, GND1.1, IC1.5 (VSS), IC2.10 (D3), IC2.12 (Uss), IC2.13 (Uee), IC2.18 (MR), IC3.10 (D3), IC3.12 (Uss), IC3.13 (Uee), IC3.18 (MR), IC4.2, IC4.5, IC4.7 (GND), IC5.7 (GND), K1.24, R24.2, T1.3 (E), T2.3 (E)
unnamed: C6.1, IC1.16 (OSC1/CLKIN), Q1.2
unnamed: C7.1, IC1.15 (OSC2/CLKOUT), Q1.1
unnamed: D1.2 (A), D3.2 (A), R21.2, R22.2, T1.2 (B)
unnamed: D2.2 (A), D4.2 (A), R23.2, T2.2 (B)
unnamed: IC1.1 (RA2), IC4.1
unnamed: IC1.2 (RA3), IC4.4
unnamed: IC1.3 (TOCKI/RA4), R13.2
unnamed: IC1.17 (RA0), R11.2
unnamed: IC1.18 (RA1), R12.2
unnamed: IC4.10, IC5.6
unnamed: IC5.3, IC5.4, IC5.9
unnamed: IC5.11, R13.1
unnamed: IC5.8, IC5.12
VCC: C1.1, C4.1, C5.1, IC1.4 (~MCLR~), IC1.14 (VDD), IC2.24 (Udd), IC3.24 (Udd), IC4.14 (VCC), IC5.14 (VCC), K1.26, R31.1, R32.1, R33.1, R34.1, R35.1, R36.1, R37.1, R38.1, VCC1.1

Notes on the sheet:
(c) MDV '97, z00m '21
